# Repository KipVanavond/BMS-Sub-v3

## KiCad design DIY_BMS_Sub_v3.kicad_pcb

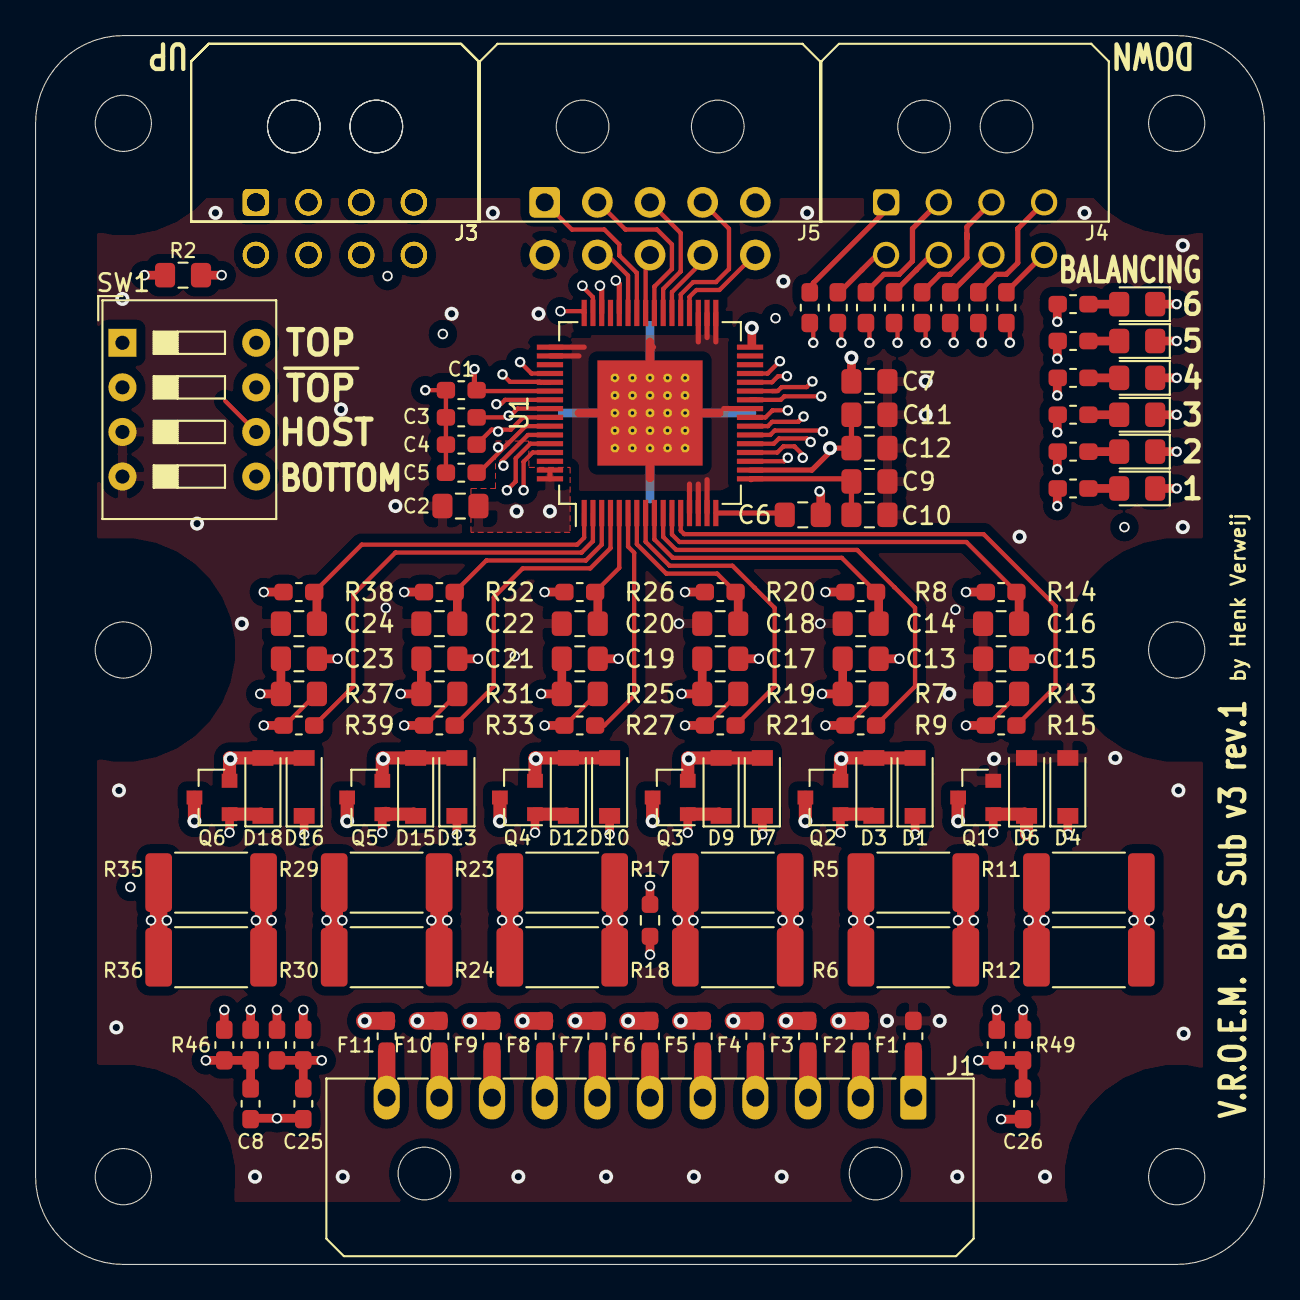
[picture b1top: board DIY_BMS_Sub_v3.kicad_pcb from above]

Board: 4 copper layers, 70.0 x 70.0 mm, 126 parts (0 on the bottom side), 95 nets.

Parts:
C1, C3, C4, C5, C8, C25, C26: 33p; C_0603_1608Metric_Pad1.05x0.95mm_HandSolder
C2, C10, C12, C13, C14, C15, C16, C17, C18, C19, C20, C21, C22, C23, C24: 0.1u; C_0805_2012Metric_Pad1.15x1.40mm_HandSolder
C6: 10u; C_0805_2012Metric_Pad1.15x1.40mm_HandSolder
C7, C9, C11: 2.2u; C_0805_2012Metric_Pad1.15x1.40mm_HandSolder
D1, D3, D4, D6, D7, D9, D10, D12, D13, D15, D16, D18: 5V6; D_SOD-123
D2, D5, D8, D11, D14, D17: LED; LED_0805_2012Metric_Pad1.15x1.40mm_HandSolder
F1, F2, F3, F4, F5, F6, F7, F8, F9, F10, F11: 2A; Fuse_0603_1608Metric_Pad1.05x0.95mm_HandSolder
H1, H2, H3, H4, H5, H6: MountingHole; MountingHole_3.2mm_M3
J1: Conn_01x11; Molex_Micro-Fit_3.0_43650-1100_1x11_P3.00mm_Horizontal
J3, J3#2, J4: Conn_02x04_Top_Bottom; Molex_Micro-Fit_3.0_43045-0800_2x04_P3.00mm_Horizontal
J5: Conn_02x05_Top_Bottom; Molex_Micro-Fit_3.0_43045-1000_2x05_P3.00mm_Horizontal
Q1, Q2, Q3, Q4, Q5, Q6: Q_NMOS_GSD; SOT-23
R1, R46, R48: 1K82; R_0603_1608Metric_Pad1.05x0.95mm_HandSolder
R2: 100K; R_0805_2012Metric_Pad1.15x1.40mm_HandSolder
R3, R47, R49: 1K47; R_0603_1608Metric_Pad1.05x0.95mm_HandSolder
R4, R10, R16, R22, R28, R34, R40, R41, R42, R43, R44, R45, R50, R51: 1k; R_0603_1608Metric_Pad1.05x0.95mm_HandSolder
R5, R6, R11, R12, R17, R18, R23, R24, R29, R30, R35, R36: 51; R_2512_6332Metric_Pad1.52x3.35mm_HandSolder
R7, R13, R19, R25, R31, R37: 1M; R_0805_2012Metric_Pad1.15x1.40mm_HandSolder
R8, R9, R14, R15, R20, R21, R26, R27, R32, R33, R38, R39: 1K; R_0603_1608Metric_Pad1.05x0.95mm_HandSolder
SW1: SW_DIP_x04; SW_DIP_SPSTx04_Slide_9.78x12.34mm_W7.62mm_P2.54mm
TH1: 10K NTC; R_0603_1608Metric_Pad0.98x0.95mm_HandSolder
U1: BQ76PL536A; HTQFP-64-1EP_10x10mm_P0.5mm_EP8x8mm_Mask4.4x4.4mm_LessTherm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

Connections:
5VDC: C7.1, C8.2, C25.2, C26.2, F8.2, F10.2, J5.5, R2.1, TH1.2, U1.32
/C1: C13.2, C15.1, D1.2, D3.2, D4.1, F2.2, Q2.2, R7.1, R10.2, R11.2, R12.2, R14.1
/C2: C13.1, C17.2, D1.1, D7.2, D9.2, F3.2, Q3.2, R4.2, R5.2, R6.2, R8.1, R19.1
/C3: C17.1, C19.2, D7.1, D10.2, D12.2, F4.2, Q4.2, R16.2, R17.2, R18.2, R20.1, R25.1
/C4: C19.1, C21.2, D10.1, D13.2, D15.2, F5.2, Q5.2, R22.2, R23.2, R24.2, R26.1, R31.1
/C5: C21.1, C23.2, D13.1, D16.2, D18.2, F6.2, Q6.2, R28.2, R29.2, R30.2, R32.1, R37.1
/C6: C2.2, C23.1, D16.1, F7.2, R34.2, R35.2, R36.2, R38.1, SW1.1, SW1.2, U1.63, U1.64
/S1_components/Balancing: R15.2, U1.12
/S1_components/VC+: C16.1, R14.2, U1.11
/S2_components/Balancing: R9.2, U1.10
/S2_components/VC+: C14.1, R8.2, U1.9
/S3_components/Balancing: R21.2, U1.8
/S3_components/VC+: C18.1, R20.2, U1.7
/S4_components/Balancing: R27.2, U1.6
/S4_components/VC+: C20.1, R26.2, U1.5
/S5_components/Balancing: R33.2, U1.4
/S5_components/VC+: C22.1, R32.2, U1.3
/S6_components/Balancing: R39.2, U1.2
/S6_components/VC+: C24.1, R38.2, U1.1
AGND: C2.1, C6.1, C7.2, C9.1, C10.2, C11.1, C12.2, C14.2, C15.2, C16.2, C18.2, C20.2, C22.2, C24.2, D4.2, D6.2, F1.2, J5.6, Q1.2, R13.1, SW1.3, SW1.4, U1.13, U1.14, U1.15, U1.25, U1.33, U1.34, U1.35, U1.49, U1.50, U1.65
ALERT_H: J5.9, U1.38
ALERT_N: C4.2, J3.7, J3#2.7, U1.57
ALERT_S: J4.7, R43.1
CONV_H: J5.10, U1.36
CONV_N: J3.8, J3#2.8, SW1.8, U1.59
CONV_S: J4.8, R45.1, SW1.5
CS_H: J5.7, U1.43
CS_N: J3.1, J3#2.1, U1.52
CS_S: J4.1, R51.1
DRDY_H: J5.4, U1.37
DRDY_N: C5.2, J3.4, J3#2.4, U1.58
DRDY_S: J4.4, R44.1
FAULT_H: J5.3, U1.39
FAULT_N: C3.2, J3.3, J3#2.3, U1.56
FAULT_S: J4.3, R42.1
LDOD: C11.2, C12.1, U1.18, U1.46
unnamed: C6.2, U1.16
unnamed: C8.1, R46.2, R47.1, U1.61
unnamed: C9.2, C10.1, U1.17
unnamed: C25.1, R1.2, R3.1, U1.20
unnamed: C26.1, R48.2, R49.1, U1.48
unnamed: D2.1, Q2.3, R5.1, R6.1
unnamed: D2.2, R4.1
unnamed: D3.1, Q2.1, R7.2, R9.1
unnamed: D5.1, Q1.3, R11.1, R12.1
unnamed: D5.2, R10.1
unnamed: D6.1, Q1.1, R13.2, R15.1
unnamed: D8.1, Q3.3, R17.1, R18.1
unnamed: D8.2, R16.1
unnamed: D9.1, Q3.1, R19.2, R21.1
unnamed: D11.1, Q4.3, R23.1, R24.1
unnamed: D11.2, R22.1
unnamed: D12.1, Q4.1, R25.2, R27.1
unnamed: D14.1, Q5.3, R29.1, R30.1
unnamed: D14.2, R28.1
unnamed: D15.1, Q5.1, R31.2, R33.1
unnamed: D17.1, Q6.3, R35.1, R36.1
unnamed: D17.2, R34.1
unnamed: D18.1, Q6.1, R37.2, R39.1
unnamed: F8.1, J1.8
unnamed: F9.1, J1.9
unnamed: F10.1, J1.10
unnamed: F11.1, J1.11
unnamed: R1.1, U1.19
unnamed: R40.2, U1.27
unnamed: R41.2, U1.26
unnamed: R42.2, U1.24
unnamed: R43.2, U1.23
unnamed: R44.2, U1.22
unnamed: R45.2, U1.21
unnamed: R46.1, U1.60
unnamed: R48.1, U1.47
unnamed: R49.2, TH1.1
unnamed: R50.2, U1.28
unnamed: R51.2, U1.29
S0: F1.1, J1.1
S1: F2.1, J1.2
S2: F3.1, J1.3
S3: F4.1, J1.4
S4: F5.1, J1.5
S5: F6.1, J1.6
S6: F7.1, J1.7
SCLK_H: J5.2, U1.40
SCLK_N: J3.6, J3#2.6, U1.55
SCLK_S: J4.6, R41.1
SDI_H: J5.1, U1.42
SDI_N: J3.5, J3#2.5, U1.53
SDI_S: J4.5, R50.1
SDO_H: J5.8, U1.41
SDO_N: C1.2, J3.2, J3#2.2, U1.54
SDO_S: J4.2, R40.1
SW_Host: R2.2, SW1.6, U1.44
SW_NotTop: C1.1, C3.1, C4.1, C5.1, SW1.7
TS1: F9.2, R3.2
TS2: F11.2, R47.2

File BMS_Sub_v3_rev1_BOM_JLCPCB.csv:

Comment,Designator,Footprint,LCSC Part Number
0.1uF,"C2,C10,C12,C13,C14,C15,C16,C17,C18,C19,C20,C21,C22,C23,C24",_0805,C49678
33pF,"C1,C3,C4,C5,C8,C25,C26",_0603,C1663
10uF,C6,_0805,C15850
2.2uF,"C7,C9,C11",_0805,C49217
Orange LED,"D2,D5,D8,D11,D14,D17",_0805,C2296
5V6 Zener,"D1,D3,D4,D6,D7,D9,D10,D12,D13,D15,D16,D18",_SOD-123,C173406
2A Fuse,"F1,F2,F3,F4,F5,F6,F7,F8,F9,F10,F11",_0603,C354889
N-ch MOSFET,"Q1,Q2,Q3,Q4,Q5,Q6",_SOT-23-3L,C20917
1K82,"R1,R46,R48",_0603,C273756
100K,R2,_0805,C25271
1K47,"R3,R47,R49",_0603,C227653
1k,"R4,R10,R16,R22,R28,R34,R40,R41,R42,R43,R44,R45,R50,R51,R8,R9,R14,R15,R20,R21,R26,R27,R32,R33,R38,R39",_0603,C21190
51,"R5,R6,R11,R12,R17,R18,R23,R24,R29,R30,R35,R36",_2512,C41977
1M,"R7,R13,R19,R25,R31,R37",_0805,C17514
10K NTC,TH1,_0603,C153011

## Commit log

2020-11-14 Add files via upload
    First upload of design.
2020-11-15 Add files via upload
    (re)labeled SPI-host pins to 10-pin connector. Added DIP-switch to South. Started placing decoupling capacitors.
2020-11-16 Add files via upload
    Finished adding decoupling caps. Added temperature sensor (TS1).
2020-11-17 Add files via upload
    Added S1 and S2 traces in IN2-layer. Added stitching vias for outside groundplanes.
2020-11-18 Add files via upload
    Added 3d models for connectors (Molex). Started changing cell connections from Top-layer to IN1-layer.
2020-11-21 Add files via upload
    Finished routing board (rev.0). Organised silkscreen labels.
2021-08-08 Add files via upload
    Additional back-up before starting Rev.1
2021-08-15 Add files via upload
    Changed board dimensions. Replaced Molex connectors from MiniFit to the smaller MicroFit-type.
2021-08-22 Add files via upload
    Placed most components. Started routing and placing vias.
2021-08-28 Add files via upload
    Routed the PCB further (switch-, NORTH- and thermistor still have to be done). Made silkscreen spacing more consistant overall. Added 3d-files for Molex-connectors.
2021-09-05 Add files via upload
    Routed external thermistor and HOST-interface traces. Added silkscreen text. Placed additional AGND-via's.
2021-09-08 Add files via upload
    Added and routed board NTC. Added connector and board info silkscreen. Made keep-out zones for AGND to remove planes under components.
2021-10-02 Add files via upload
    Placed additional via's to BQ76-IC and removed soldermask beneath (to allow for soldering of thermal pad without hot air). Generated GERBER-, BOM- (for SMD parts) and POS-file.
2021-10-14 Add files via upload
    Checked clearances and order files.
    Last change of revison 1.
    Ordered PCB and started programming/testing.
